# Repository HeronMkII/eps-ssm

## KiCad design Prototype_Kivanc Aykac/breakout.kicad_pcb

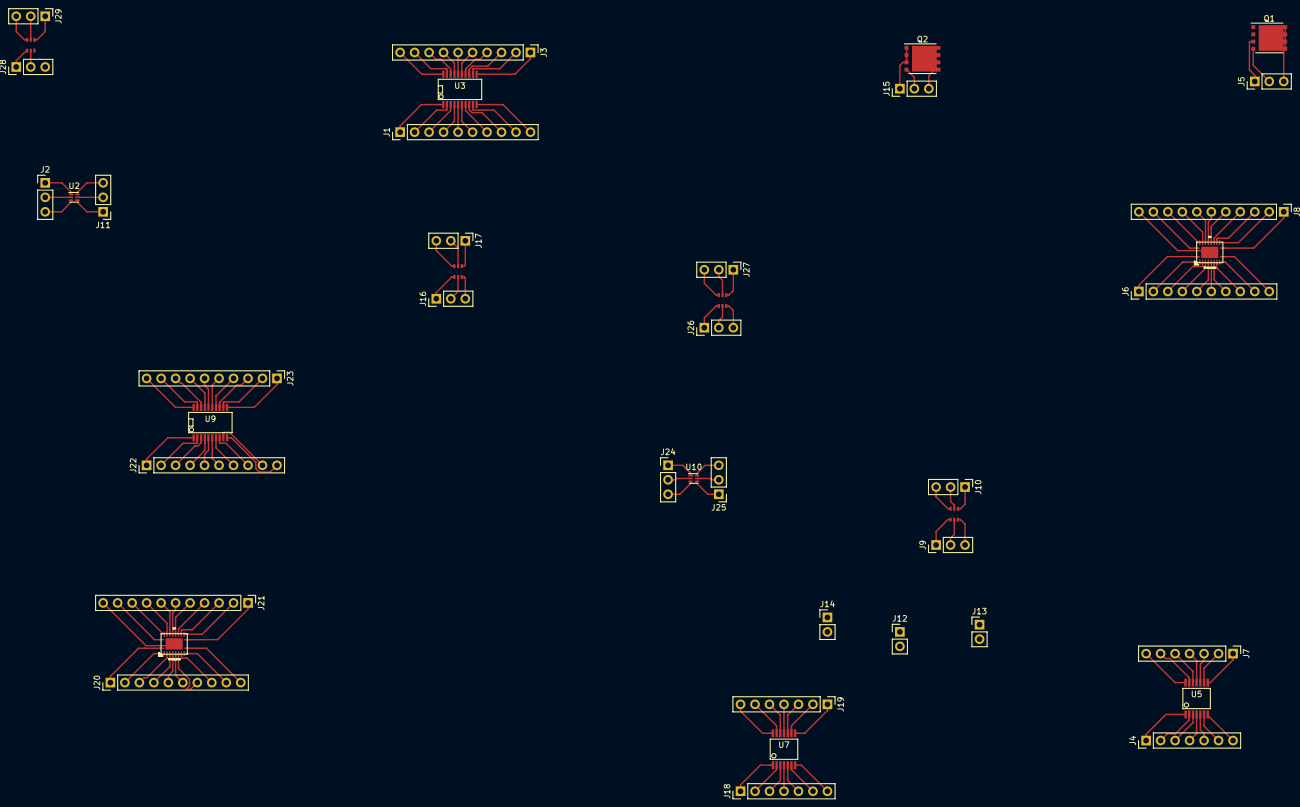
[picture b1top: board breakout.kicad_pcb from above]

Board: 2 copper layers, 43 parts (0 on the bottom side), 152 nets.

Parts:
J1, J3, J6, J20, J22, J23: Conn_01x10_Male; Pin_Header_Straight_1x10_Pitch2.54mm
J2, J5, J9, J10, J11, J15, J16, J17, J24, J25, J26, J27, J28, J29: Conn_01x03_Male; Pin_Header_Straight_1x03_Pitch2.54mm
J4, J7, J18, J19: Conn_01x07_Male; Pin_Header_Straight_1x07_Pitch2.54mm
J8, J21: Conn_01x11_Male; Pin_Header_Straight_1x11_Pitch2.54mm
J12, J13, J14: Conn_01x02_Male; Pin_Header_Straight_1x02_Pitch2.54mm
Q1, Q2: BSC026NE2LS5; VSONP-8-1EP_5x6_Pitch1.27mm
U1, U6, U11, U12: INA214; SC70-6
U2, U10: bq297xx; WSON6_1.5x1.5mm_Pitch0.5mm
U3, U9: LM21215; SSOP-20
U4, U8: TPS61088; pvqfn-n20
U5, U7: ADA4891-4; SSOP-14

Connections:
unnamed: J1.1, U3.1
unnamed: J1.2, U3.2
unnamed: J1.3, U3.3
unnamed: J1.4, U3.4
unnamed: J1.5, U3.5
unnamed: J1.6, U3.6
unnamed: J1.7, U3.7
unnamed: J1.8, U3.8
unnamed: J1.9, U3.9
unnamed: J1.10, U3.10
unnamed: J2.1, U2.1
unnamed: J2.2, U2.2
unnamed: J2.3, U2.3
unnamed: J3.1, U3.11
unnamed: J3.2, U3.12
unnamed: J3.3, U3.13
unnamed: J3.4, U3.14
unnamed: J3.5, U3.15
unnamed: J3.6, U3.16
unnamed: J3.7, U3.17
unnamed: J3.8, U3.18
unnamed: J3.9, U3.19
unnamed: J3.10, U3.20
unnamed: J4.1, U5.1
unnamed: J4.2, U5.2
unnamed: J4.3, U5.3
unnamed: J4.4, U5.4
unnamed: J4.5, U5.5
unnamed: J4.6, U5.6
unnamed: J4.7, U5.7
unnamed: J5.1, Q1.1
unnamed: J5.2, Q1.2
unnamed: J5.3, Q1.3
unnamed: J6.1, U4.1
unnamed: J6.2, U4.2
unnamed: J6.3, U4.3
unnamed: J6.4, U4.4
unnamed: J6.5, U4.5
unnamed: J6.6, U4.6
unnamed: J6.7, U4.7
unnamed: J6.8, U4.8
unnamed: J6.9, U4.9
unnamed: J6.10, U4.10
unnamed: J7.1, U5.8
unnamed: J7.2, U5.9
unnamed: J7.3, U5.10
unnamed: J7.4, U5.11
unnamed: J7.5, U5.12
unnamed: J7.6, U5.13
unnamed: J7.7, U5.14
unnamed: J8.1, U4.11
unnamed: J8.2, U4.12
unnamed: J8.3, U4.13
unnamed: J8.4, U4.14
unnamed: J8.5, U4.15
unnamed: J8.6, U4.16
unnamed: J8.7, U4.17
unnamed: J8.8, U4.18
unnamed: J8.9, U4.19
unnamed: J8.10, U4.20
unnamed: J8.11, U4.21
unnamed: J9.1, U1.1
unnamed: J9.2, U1.2
unnamed: J9.3, U1.3
unnamed: J10.1, U1.4
unnamed: J10.2, U1.5
unnamed: J10.3, U1.6
unnamed: J11.1, U2.4
unnamed: J11.2, U2.5
unnamed: J11.3, U2.6
unnamed: J15.1, Q2.1
unnamed: J15.2, Q2.2
unnamed: J15.3, Q2.3
unnamed: J16.1, U6.1
unnamed: J16.2, U6.2
unnamed: J16.3, U6.3
unnamed: J17.1, U6.4
unnamed: J17.2, U6.5
unnamed: J17.3, U6.6
unnamed: J18.1, U7.1
unnamed: J18.2, U7.2
unnamed: J18.3, U7.3
unnamed: J18.4, U7.4
unnamed: J18.5, U7.5
unnamed: J18.6, U7.6
unnamed: J18.7, U7.7
unnamed: J19.1, U7.8
unnamed: J19.2, U7.9
unnamed: J19.3, U7.10
unnamed: J19.4, U7.11
unnamed: J19.5, U7.12
unnamed: J19.6, U7.13
unnamed: J19.7, U7.14
unnamed: J20.1, U8.1
unnamed: J20.2, U8.2
unnamed: J20.3, U8.3
unnamed: J20.4, U8.4
unnamed: J20.5, U8.5
unnamed: J20.6, U8.6
unnamed: J20.7, U8.7
unnamed: J20.8, U8.8
unnamed: J20.9, U8.9
unnamed: J20.10, U8.10
unnamed: J21.1, U8.11
unnamed: J21.2, U8.12
unnamed: J21.3, U8.13
unnamed: J21.4, U8.14
unnamed: J21.5, U8.15
unnamed: J21.6, U8.16
unnamed: J21.7, U8.17
unnamed: J21.8, U8.18
unnamed: J21.9, U8.19
unnamed: J21.10, U8.20
unnamed: J21.11, U8.21
unnamed: J22.1, U9.1
unnamed: J22.2, U9.2
unnamed: J22.3, U9.3
unnamed: J22.4, U9.4
unnamed: J22.5, U9.5
unnamed: J22.6, U9.6
unnamed: J22.7, U9.7
unnamed: J22.8, U9.8
unnamed: J22.9, U9.9
unnamed: J22.10, U9.10
unnamed: J23.1, U9.11
unnamed: J23.2, U9.12
unnamed: J23.3, U9.13
unnamed: J23.4, U9.14
unnamed: J23.5, U9.15
unnamed: J23.6, U9.16
unnamed: J23.7, U9.17
unnamed: J23.8, U9.18
unnamed: J23.9, U9.19
unnamed: J23.10, U9.20
unnamed: J24.1, U10.1
unnamed: J24.2, U10.2
unnamed: J24.3, U10.3
unnamed: J25.1, U10.4
unnamed: J25.2, U10.5
unnamed: J25.3, U10.6
unnamed: J26.1, U11.1
unnamed: J26.2, U11.2
unnamed: J26.3, U11.3
unnamed: J27.1, U11.4
unnamed: J27.2, U11.5
unnamed: J27.3, U11.6
unnamed: J28.1, U12.1
unnamed: J28.2, U12.2
unnamed: J28.3, U12.3
unnamed: J29.1, U12.4
unnamed: J29.2, U12.5
unnamed: J29.3, U12.6

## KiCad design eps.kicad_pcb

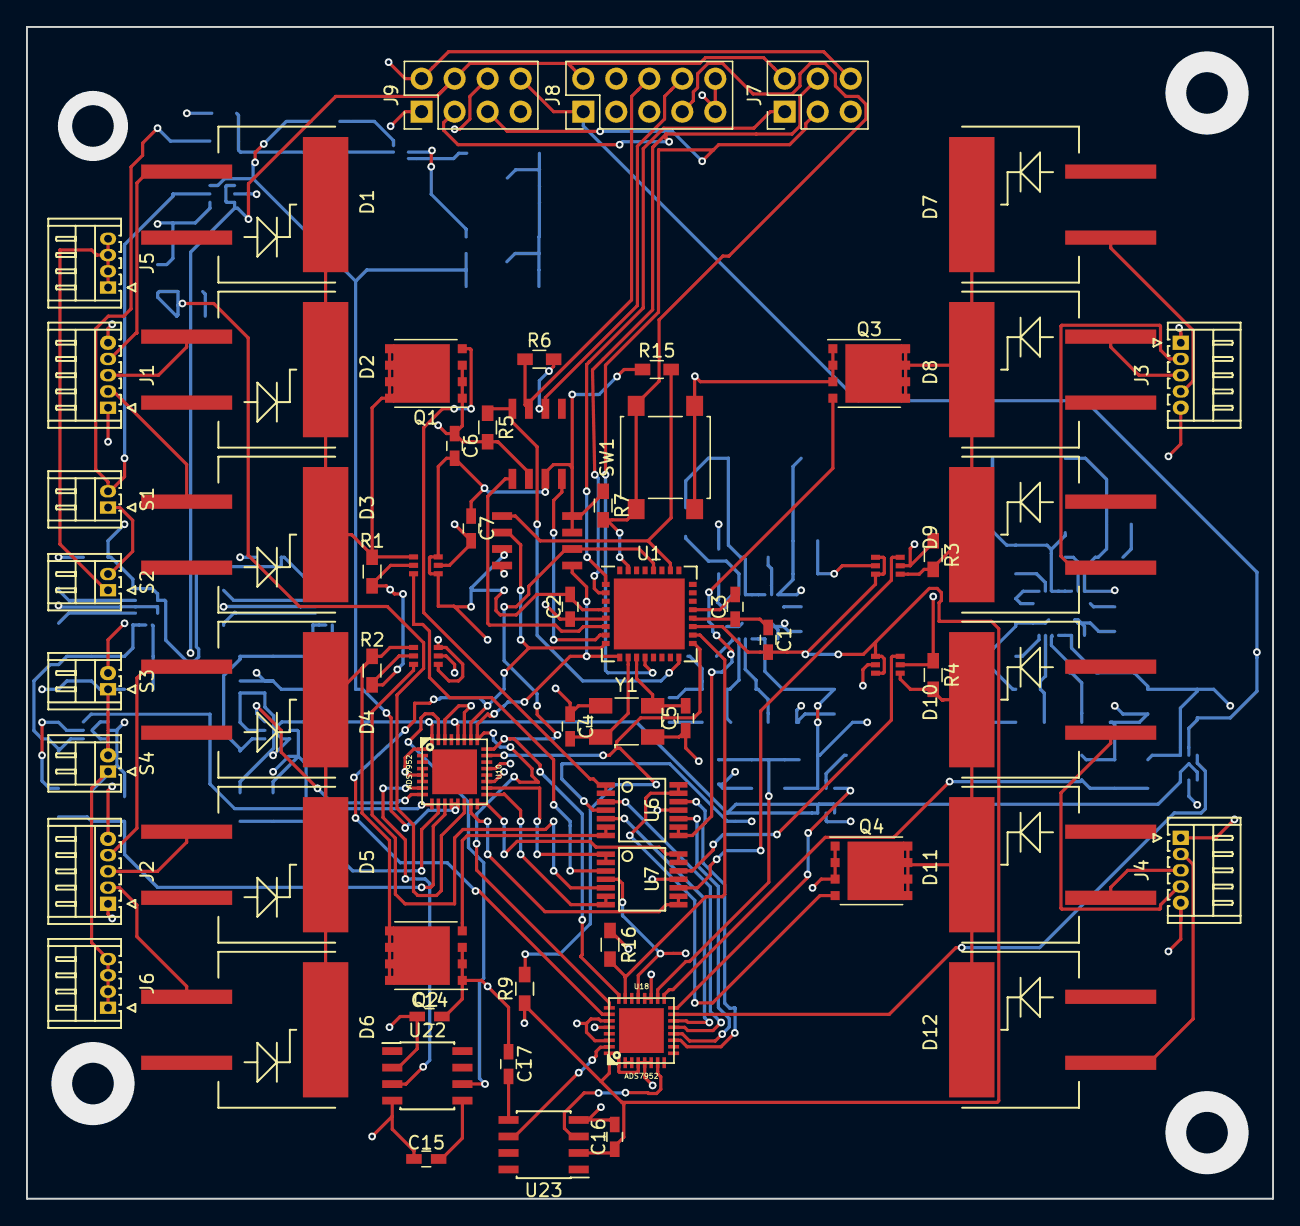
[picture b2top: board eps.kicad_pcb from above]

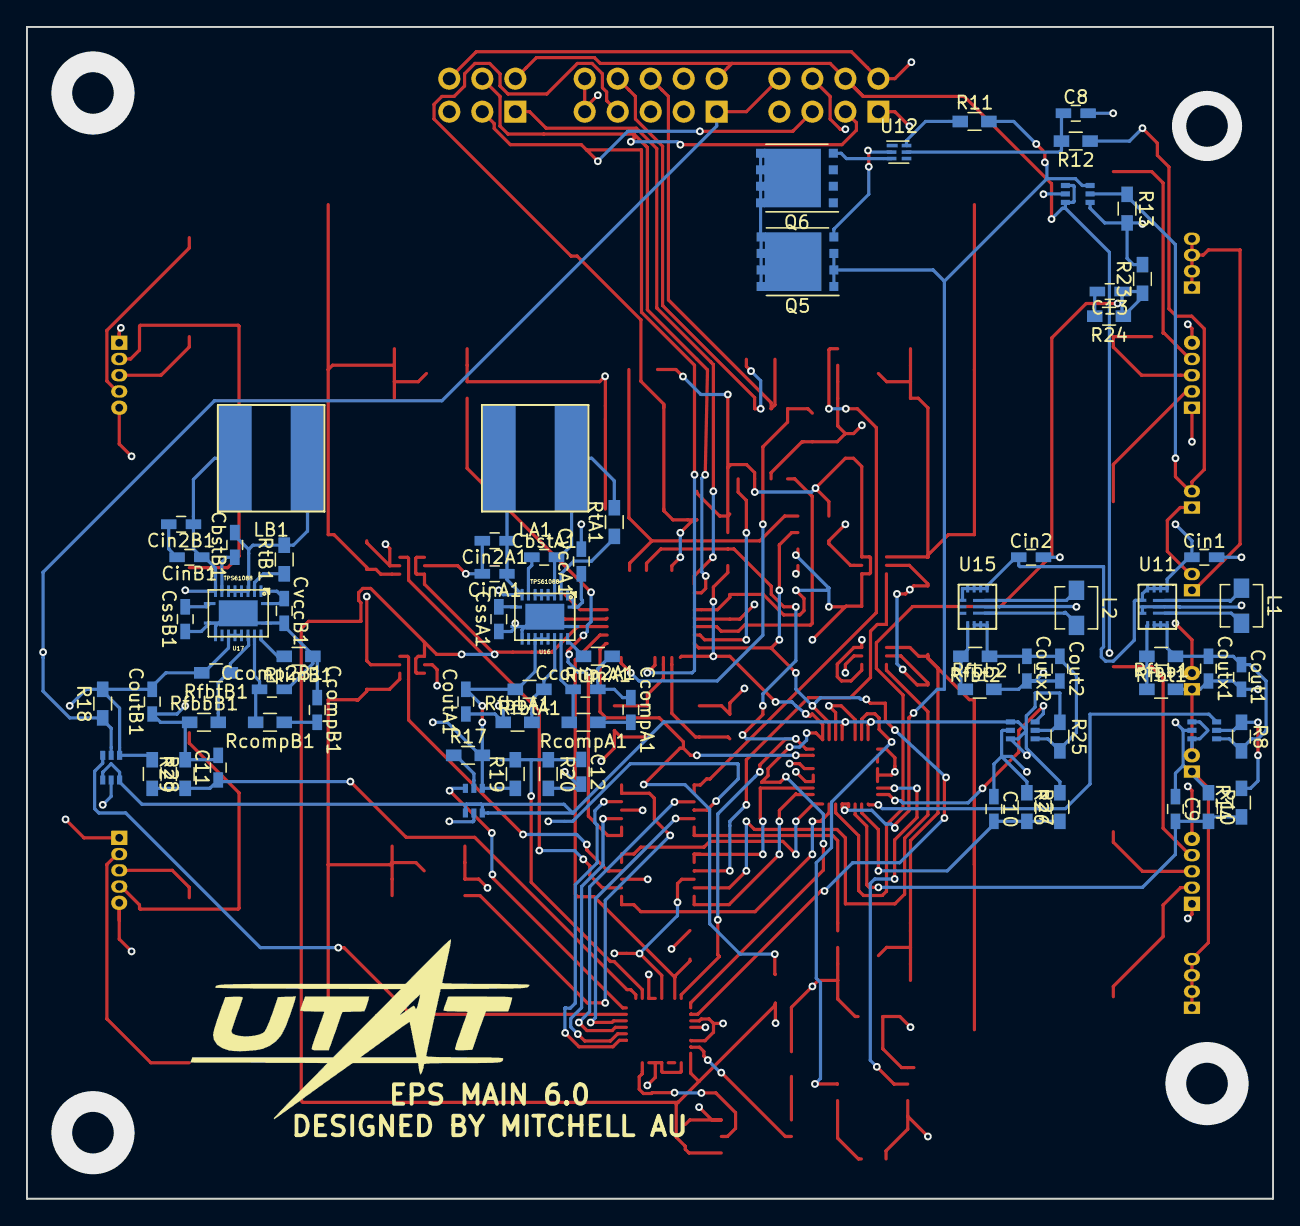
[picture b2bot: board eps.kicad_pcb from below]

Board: 4 copper layers, 95.9 x 90.2 mm, 140 parts (75 on the bottom side), 109 nets.

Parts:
C1, C2, C3, C6: 0.1µF; C_0603_HandSoldering
C4, C5: 22pF; C_0603_HandSoldering
C7: 100nF; C_0603_HandSoldering
C8: 0.1uF; C_0603_HandSoldering
C9, C10, C11, C12: C_Small; C_0603_HandSoldering
C13: C_small; C_0603_HandSoldering
C14, C16: 10µ; C_0603_HandSoldering
C15, C17: 1µ; C_0603_HandSoldering
CbstA1: 100nF; C_0603_HandSoldering
CbstB1: 100nF; C_0603_HandSoldering
Ccomp2A1, Ccomp2B1: 82pF; C_0603_HandSoldering
CcompA1: 1.8nF; C_0603_HandSoldering
CcompB1: 1.8nF; C_0603_HandSoldering
Cin1, Cin2: 10.0µF; C_0603_HandSoldering
Cin2A1, Cin2B1: 100n; C_0603_HandSoldering
CinA1: 12µF; C_0603_HandSoldering
CinB1: 12µF; C_0603_HandSoldering
Cout1, Cout2: 47.0µF; C_0603_HandSoldering
CoutA1: 47µF; C_0603_HandSoldering
CoutB1: 47µF; C_0603_HandSoldering
Coutx1, Coutx2: 10.0µF; C_0603_HandSoldering
CssA1: 8.2nF; C_0603_HandSoldering
CssB1: 8.2nF; C_0603_HandSoldering
CvccA1: 1µF; C_0603_HandSoldering
CvccB1: 1µF; C_0603_HandSoldering
D1, D2, D3, D4, D5, D6, D7, D8, D9, D10, D11, D12: SM74611; DD-PAK_TO263_SingleDiode
J1, J2, J3, J4: CONN_01X05; Hirose_DF13-05P-1.25DS_05x1.25mm_Angled
J5: +BATT; Hirose_DF13-04P-1.25DS_04x1.25mm_Angled
J6: -BATT; Hirose_DF13-04P-1.25DS_04x1.25mm_Angled
J7: PROGRAMMING PORT; Pin_Header_Straight_2x03_Pitch2.54mm
J8: H_EPS; Pin_Header_Straight_2x05_Pitch2.54mm
J9: DEBUG; Pin_Header_Straight_2x04_Pitch2.54mm
L1, L2: 1.0µH; L_Vishay_IHLP-1212
LA1: 2.2µH; SRN8040
LB1: 2.2µH; SRN8040
Q1, Q2, Q3, Q4, Q5, Q6: BSC026NE2LS5; VSONP-8-1EP_5x6_Pitch1.27mm
R1, R2, R3, R4, R8, R25: 10mΩ; R_0603_HandSoldering
R5: 1kΩ; R_0603_HandSoldering
R6: 120Ω; R_0603_HandSoldering
R7, R13: 10kΩ; R_0603_HandSoldering
R9, R15, R16: 10k; R_0603_HandSoldering
R10, R14, R19, R20, R26, R27, R28, R29: R_Small; R_0603_HandSoldering
R11: 2.2k; R_0603_HandSoldering
R12: 330; R_0603_HandSoldering
R17, R18: 10m; R_0603_HandSoldering
R23, R24: R; R_0603_HandSoldering
RcompA1: 15.8kΩ; R_0603_HandSoldering
RcompB1: 15.8kΩ; R_0603_HandSoldering
Rfbb1, Rfbb2: 180k; R_0603_HandSoldering
RfbbA1: 69.8kΩ; R_0603_HandSoldering
RfbbB1: 69.8kΩ; R_0603_HandSoldering
Rfbt1, Rfbt2: 562k; R_0603_HandSoldering
RfbtA1: 220k; R_0603_HandSoldering
RfbtB1: 220k; R_0603_HandSoldering
RlimA1: 162kΩ; R_0603_HandSoldering
RlimB1: 162kΩ; R_0603_HandSoldering
RtA1: 267kΩ; R_0603_HandSoldering
RtB1: 267kΩ; R_0603_HandSoldering
S1, S2, S3: DEP. SWITCH; Hirose_DF13-02P-1.25DS_02x1.25mm_Angled
S4: RBL PIN; Hirose_DF13-02P-1.25DS_02x1.25mm_Angled
SW1: SW_RST; SW_SPST_B3S-1000
U1: ATMEGA32M1-MU; QFN-32-1EP_7x7mm_Pitch0.65mm
U2, U3, U4, U5, U13, U14, U19, U20, U21: INA214; SC70-6
U6, U7: ADA4891-4; SSOP-14
U8: SN65HVD230; SOIC8
U9: SST25VF016B; SOIC8
U10, U18: ADS7952; pvqfn-n32
U11, U15: TPS630250; VQFN-14
U12: bq297xx; WSON6_1.5x1.5mm_Pitch0.5mm
U16, U17: TPS61088; pvqfn-n20
U22, U23: REF5025; SOIC-8_3.9x4.9mm_Pitch1.27mm
Y1: 8MHz; Crystal_SMD_Abracon_ABM3B-4pin_5.0x3.2mm

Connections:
+3V3: C1.2, C2.2, C3.2, C6.2, C7.1, C14.1, C16.1, J7.2, J8.2, J9.4, R7.1, R8.1, R9.1, R14.2, R15.1, R16.1, R25.1, R26.2, U1.4, U1.19, U1.21, U2.1, U2.3, U3.1, U3.3, U4.1, U4.3, U5.1, U5.3, U8.3, U9.3, U9.7, U9.8, U10.21, U10.28, U10.32, U13.1, U13.3, U14.1, U14.3, U14.5, U18.21, U18.28, U18.32, U19.1, U19.3, U19.5, U20.1, U20.3, U21.1, U21.3, U22.2, U23.2
+5V: J8.1, J9.8, R17.1, R18.1, U6.4, U7.4, U20.5, U21.5
+PACK: Cin1.1, Cin2.1, Cin2A1.1, Cin2B1.1, CinA1.1, CinB1.1, J9.6, LA1.1, LB1.1, R1.1, R2.1, R3.1, R4.1, R13.2, R23.1, U2.5, U3.5, U4.5, U5.5, U11.4, U11.5, U11.6, U11.7, U11.8, U13.4, U15.4, U15.5, U15.6, U15.7, U15.8, U16.9, U17.9
-PACK: Q5.1, R11.2, U10.12, U10.13, U13.6
/2V5A: U10.31, U22.6
/2V5B: U18.31, U23.6
/3V3IOUT1: U10.9, U14.6
/3V3IOUT2: U10.8, U19.6
/3V3VOUT1: C9.2, R10.2, R14.1, U10.11
/3V3VOUT2: C10.2, R26.1, R27.2, U10.10
/+XI: U7.1, U7.2, U10.18
/+XVgs: U6.3, U18.13
/+YI: U7.13, U7.14, U10.16
/+YVgs: U6.12, U18.11
/-XI: U7.6, U7.7, U10.17
/-XVgs: U6.5, U18.14
/-YI: U7.8, U7.9, U10.15
/-YVgs: U6.10, U18.12
/CANH: J8.6, R6.1, U8.7
/CANL: J8.8, R6.2, U8.6
/CAN_LPWR: R5.1, U1.16, U8.8
/CAN_RX: U1.7, U8.4
/CAN_TX: U1.6, U8.1
/CS_ADC1: R9.2, U1.17, U10.23
/CS_ADC2: R16.2, U1.18, U18.23
/CS_MEM: R15.2, U1.26, U9.1
/EPS_RST: J8.7, R7.2, SW1.1, U1.31
/IOUTA: U18.16, U20.6
/IOUTB: U18.15, U21.6
/MISO: U1.8, U9.2, U10.26, U18.26
/MISO_A: J7.1, U1.1
/MOSI: U1.9, U9.5, U10.25, U18.25
/MOSI_A: J7.4, J9.3
/SCK: U1.28, U9.6, U10.24, U18.24
/SCK_A: J7.3, J9.5
/TEMPA: U10.7, U22.3
/TEMPB: U18.7, U23.3
/VOLT5VA: C12.1, R19.2, R20.1, U18.18
/VOLT5VB: C11.1, R28.2, R29.1, U18.17
/VPACK: C13.1, R23.2, R24.1, U10.14
GND: C1.1, C2.1, C3.1, C4.1, C5.1, C6.1, C7.2, C8.2, C9.1, C10.1, C11.2, C12.2, C13.2, C14.2, C15.1, C16.2, C17.1, Ccomp2A1.2, Ccomp2B1.2, CcompA1.1, CcompB1.1, Cin1.2, Cin2.2, Cin2A1.2, Cin2B1.2, CinA1.2, CinB1.2, Cout1.2, Cout2.2, CoutA1.1, CoutB1.1, Coutx1.2, Coutx2.2, CssA1.1, CssB1.1, CvccA1.2, CvccB1.2, J1.1, J1.5, J2.1, J2.5, J3.1, J3.5, J4.1, J4.5, J7.6, J8.9, J8.10, J9.1, J9.2, Q1.1, Q2.1, Q3.1, Q4.1, Q6.1, R5.2, R10.1, R20.2, R24.2, R27.1, R29.2, Rfbb1.2, Rfbb2.2, RfbbA1.1, RfbbB1.1, RlimA1.1, RlimB1.1, S3.2, SW1.2, U1.5, U1.20, U2.2, U3.2, U4.2, U5.2, U6.11, U7.11, U8.2, U9.4, U10.1, U10.4, U10.5, U10.6, U10.19, U10.20, U10.22, U10.27, U10.30, U11.2, U11.9, U11.10, U12.4, U13.2, U14.2, U15.2, U15.9, U15.10, U16.11, U16.12, U16.20, U16.21, U17.11, U17.12, U17.20, U17.21, U18.1, U18.4, U18.5, U18.6, U18.19, U18.20, U18.22, U18.27, U18.30, U19.2, U20.2, U21.2, U22.4, U23.4, Y1.2, Y1.4
unnamed: C4.2, U1.10, Y1.1
unnamed: C5.2, U1.11, Y1.3
unnamed: C8.1, R12.2, U12.5
unnamed: C15.2, U22.5
unnamed: C17.2, U23.5
unnamed: CbstA1.1, U16.8
unnamed: CbstA1.2, LA1.2, RtA1.2, U16.4, U16.5, U16.6, U16.7
unnamed: CbstB1.1, U17.8
unnamed: CbstB1.2, LB1.2, RtB1.2, U17.4, U17.5, U17.6, U17.7
unnamed: Ccomp2A1.1, RcompA1.2, U16.18
unnamed: Ccomp2B1.1, RcompB1.2, U17.18
unnamed: CcompA1.2, RcompA1.1
unnamed: CcompB1.2, RcompB1.1
unnamed: Cout1.1, Coutx1.1, R8.2, Rfbt1.1, U11.12, U11.13, U11.14, U14.4
unnamed: Cout2.1, Coutx2.1, R25.2, Rfbt2.1, U15.12, U15.13, U15.14, U19.4
unnamed: CoutA1.2, R17.2, R19.1, RfbtA1.2, U16.14, U16.15, U16.16, U20.4
unnamed: CoutB1.2, R18.2, R28.1, RfbtB1.2, U17.14, U17.15, U17.16, U21.4
unnamed: CssA1.2, U16.10
unnamed: CssB1.2, U17.10
unnamed: CvccA1.1, U16.1, U16.2
unnamed: CvccB1.1, U17.1, U17.2
unnamed: D1.1, J1.4
unnamed: D1.2, D2.2, D3.2, Q1.3, R1.2, U2.4
unnamed: D2.1, J1.3
unnamed: D3.1, J1.2
unnamed: D4.1, J2.4
unnamed: D4.2, D5.2, D6.2, Q2.3, R2.2, U3.4
unnamed: D5.1, J2.3
unnamed: D6.1, J2.2
unnamed: D7.1, J3.4
unnamed: D7.2, D8.2, D9.2, Q3.3, R3.2, U4.4
unnamed: D8.3, J3.3
unnamed: D9.1, J3.2
unnamed: D10.1, J4.4
unnamed: D10.2, D11.2, D12.2, Q4.3, R4.2, U5.4
unnamed: D11.1, J4.3
unnamed: D12.1, J4.2
unnamed: J5.1, J5.2, J5.3, J5.4, S2.1
unnamed: J6.1, J6.2, J6.3, J6.4, S4.1
unnamed: L1.1, U11.3
unnamed: L1.2, U11.1
unnamed: L2.1, U15.3
unnamed: L2.2, U15.1
unnamed: Q1.2, U6.1, U6.2
unnamed: Q2.2, U6.6, U6.7
unnamed: Q3.2, U6.8, U6.9
unnamed: Q4.2, U6.13, U6.14
unnamed: Q5.2, U12.2
unnamed: Q5.3, Q6.3
unnamed: Q6.2, U12.3
unnamed: R11.1, U12.6
unnamed: R12.1, R13.1, S1.2, U13.5
unnamed: Rfbb1.1, Rfbt1.2, U11.11
unnamed: Rfbb2.1, Rfbt2.2, U15.11
unnamed: RfbbA1.2, RfbtA1.1, U16.17
unnamed: RfbbB1.2, RfbtB1.1, U17.17
unnamed: RlimA1.2, U16.19
unnamed: RlimB1.2, U17.19
unnamed: RtA1.1, U16.3
unnamed: RtB1.1, U17.3
unnamed: S1.1, S2.2
unnamed: S3.1, S4.2
unnamed: U2.6, U7.3
unnamed: U3.6, U7.5
unnamed: U4.6, U7.10
unnamed: U5.6, U7.12
unnamed: U10.2, U10.3
unnamed: U18.2, U18.3

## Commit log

2017-11-11 Initial commit
    Initial commit
2017-11-16 Test commit
    Wrote hello
2017-11-16 Test return
    Changed note to "Hi back"
2017-11-16 Test commit in the terminal
2017-11-18 Changed footprint of TPS61088
    Will reconstruct boost converter circuit
2017-11-18 BPack Ammeter + Proctection Circuit Edit
    Added ammeter to battery pack input. Removed wire from +PACK to batteries 2 and 3 (all batteries should now be protected).
2017-11-18 (Confirmation) BPack Ammeter + Proctection Circuit Edit
    Making sure the last commit pushed all edits.
2017-11-25 Ammetre addition
    Ammetres added to 3V3 buck converter. Naming convention added for 3V3 1 and 2.
2017-11-25 Boost converter
    Changed output voltage from 12V to 9V
2017-11-25 Battery Pack Edits
    - Fixed hierarchy label errors (output to input)
    - Added Voltmeter to Battery Pack Schematic
2017-11-25 Minor Edits
    Took out a comment, edited other comments
2017-11-25 Gantt Chart
2017-11-25 Boost converter completed
    All values are calculated
2017-12-02 MATLAB files
    Initial commit for MATLAB files
2017-12-02 SWITCH_3V3
    Added emergency switch circuit for 3V3 loads.
2017-12-02 Re-add BATT.sch
2017-12-02 Renamed Vg signal to 3V3_SWITCH
    To avoid conflict with the 9V Switch box
2017-12-02 Added 9V Switch
    Added switch to 9V, identical to the 3.3V.
    Changed N_3.3V and E_3.3V from input to output.
2017-12-05 Voltmeters added to 3V3 and 9V
    Added 4 voltmeters. Outputs still need to be added to hierarchical sheets.
2017-12-29 Edits to Hierarchical Labels
    Added hierarchical labels and changed some in/out directions. Not entirely sure about PV and BP labels.
2017-12-30 Datasheets
    Added datasheets for 18650 and solar cell
2017-12-30 Completed charge controller circuit
    Batteries are now on a separate board, and will connect to the EPS
    board through header pins. Charge controller circuit was implemented
    according to the datasheet.
2017-12-30 "Created a model of the sattelite for lighting simulations"
2018-01-06 Added pulldown resistors
2018-01-20 Prototype
    Started laying out breakout boards
2018-01-20 Test
    hello
2018-01-22 Finished laying out breakout boards
2018-01-23 Updated Gantt Chart
2018-01-24 changed 'program pcb' to 'program µC'
2018-01-24 Changed footprint of TPS61088
    Also added a dot beside pin 1 of INA214
2018-01-25 Dummy commit
    To make the error go away
2018-02-03 Created netlist
    Still missing deployment and RBL switches
2018-02-03 hello
2018-02-03 Removed matlab files
2018-02-03 Replaced layout file with that from bus-pcbs
2018-02-03 Began interfacing with µC
    Also all 9V should now be 5V, change resistors accordingly.
2018-02-08 PCB layout as of 2018-02-07
2018-02-12 PCB layout as of 2018-02-12
    All that’s left to do is add deployment switches
2018-02-13 Refilled pours
2018-02-14 copy of breakout for myself
2018-02-14 Added deployment/RBL switches and debug headers to EPS board
2018-02-15 Replaced battery connectors with DF13
2018-02-15 fixed gnd pour over corner holes
    I think I didn't break anything
2018-02-15 Exported EPS board
2018-02-17 Save checkpoint
    Deleted warning text. If anything dies please revert to this version!
2018-02-17 Added REF5025 for 2.5V reference for ADCs
2018-02-18 updated gbr files
2018-02-18 Merge remote-tracking branch 'origin/master'
    # Conflicts:
    # Board.zip
    # Board/eps-B.Cu.gbr
    # Board/eps-B.Mask.gbr
    # Board/eps-B.SilkS.gbr
    # Board/eps-Edge.Cuts.gbr
2018-02-19 Ground Pour, Pad Clearance
    Fixed the ground pour, fixed pad clearances on connectors because DFMcheck was mad about it
2018-02-19 repour again
2018-02-19 Resized pads
    J2, J3, J4, S4
    X = 1.1 mm
2018-02-28 breakout changes for myself
2018-02-28 Completed the breakout for myself
2018-03-06 Prototype_Jaden folder added
    Added file for personal breakout board testing.
2018-03-07 Mo Breakout Boards Practice
    Practice breakout boards
2018-03-10 Added/Removed Misc Datasheets
    Added TPS630250 and removed TPS 630242 design.
2018-04-21 Exported kicad schematics to pdf
